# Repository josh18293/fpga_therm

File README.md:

# fpga_therm
Thermal Runaway Prevention Using an FPGA

Verilog/C code goes here

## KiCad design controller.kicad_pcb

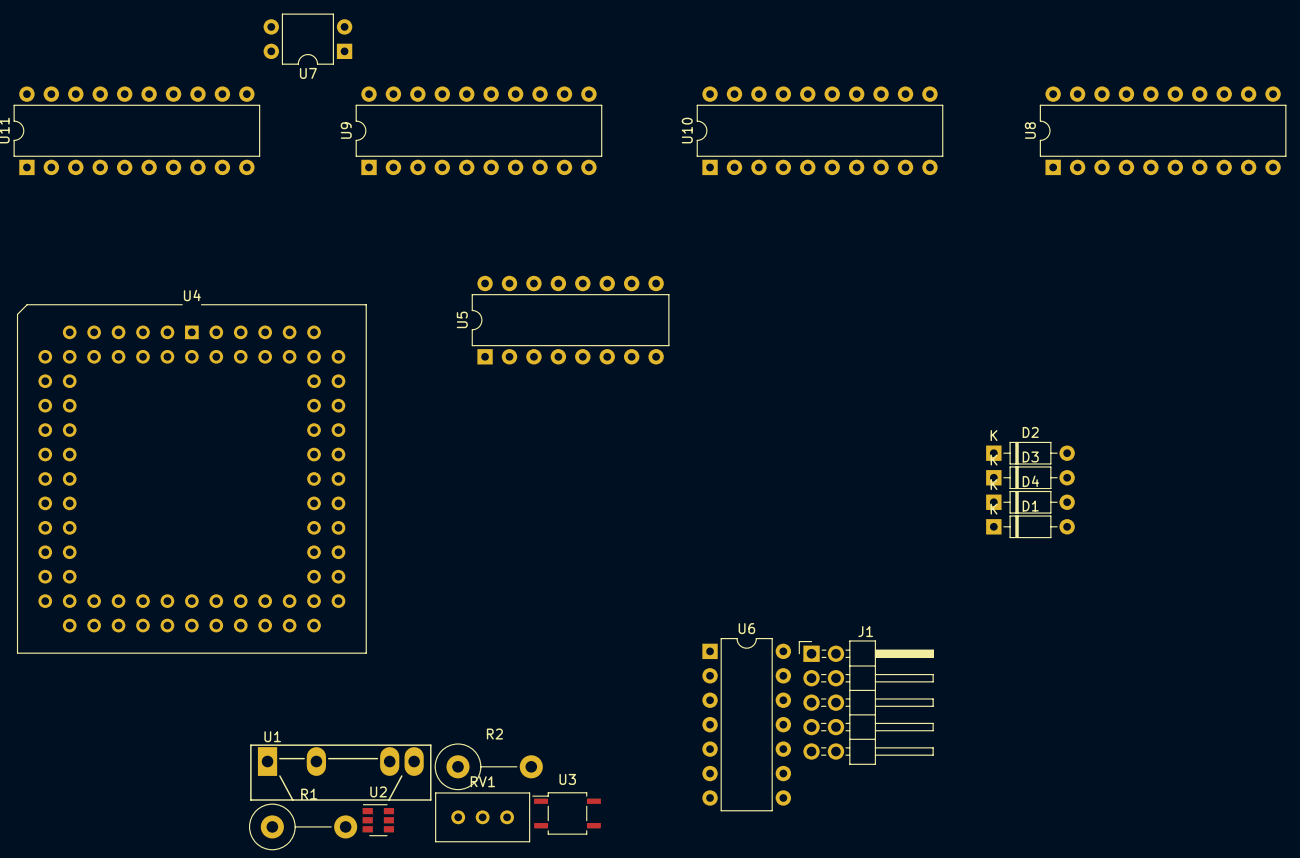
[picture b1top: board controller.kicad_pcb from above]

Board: 2 copper layers, 19 parts (0 on the bottom side), 18 nets, no tracks yet.

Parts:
D1, D2, D3, D4: 1N914; D_DO-35_SOD27_P7.62mm_Horizontal
J1: JTAG CONNECTOR; PinHeader_2x05_P2.54mm_Horizontal
R1: 100K; R_Axial_DIN0414_L11.9mm_D4.5mm_P7.62mm_Vertical
R2: 110K; R_Axial_DIN0414_L11.9mm_D4.5mm_P7.62mm_Vertical
RV1: 50K; Potentiometer_Bourns_3296W_Vertical
U1: S102S01; SIP4_Sharp-SSR_P7.62mm_Straight
U2: TPS22929D; SOT-23-6
U3: CPC1004N; SOP-4_3.8x4.1mm_P2.54mm
U4: EPM7128SLC84; PLCC-84_THT-Socket
U5: 74LS139; DIP-16_W7.62mm
U6: 74LS21; DIP-14_W7.62mm
U7: LM741; DIP-4_W7.62mm
U8: ADC0804_0; DIP-20_W7.62mm
U9: ADC0804_2; DIP-20_W7.62mm
U10: ADC0804_1; DIP-20_W7.62mm
U11: ADC0804_3; DIP-20_W7.62mm

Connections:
BNK_0+: D1.2, U8.6
BNK_1+: D3.2, U10.6
BNK_2+: D2.2, U9.6
BNK_3+: D4.2, U11.6
GND: R2.2, U4.7, U4.19, U4.32, U4.42, U4.47, U4.59, U4.72, U4.82, U5.1, U7.4, U8.10, U9.10, U10.10, U11.10
GNDA: U8.8, U9.8, U10.8, U11.8
unnamed: R1.2, RV1.1, U7.3
unnamed: R2.1, RV1.2, RV1.3
VCC: D1.1, D2.1, D3.1, D4.1, R1.1, U4.3, U4.13, U4.26, U4.38, U4.43, U4.53, U4.66, U4.78, U5.13, U5.14, U5.15, U6.9, U6.10, U6.12, U6.13, U8.20, U9.20, U10.20, U11.20
VREF_2: U7.2, U8.9, U9.9, U10.9, U11.9
~ADC_0: U5.4, U8.1
~ADC_1: U5.5, U10.1
~ADC_2: U5.6, U9.1
~ADC_3: U5.7, U11.1
~INT_0: U6.5, U8.5
~INT_1: U6.4, U10.5
~INT_2: U6.2, U9.5
~INT_3: U6.1, U11.5

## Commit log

2019-02-18 Add files via upload
    Arduino sketch of prototype
